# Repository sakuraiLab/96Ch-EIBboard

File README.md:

# 96-channel EIB board
Yuma Osako, Doshisha University (2021)
Tomoya Ohnuki, Kazuki Shiotani, Yuta Tanisumi, Shogo Takamiya

This package is provided free under the terms of the Creative Commons Attribution-NonCommercial-ShareAlike 3.0 IGO License.

This blueprint was generated for the electrophysiological recording of the mice/rats using tetrodes (96ch, 24 tetrodes).

## References
OpenEphys 
An easy-to-assemble, robust, and lightweight drive implant for chronic tetrode recordings in freely moving animals J Voigts, JP Newman, MA Wilson, MT Harnett Journal of Neural Engineering 17 (2), 026044 (https://iopscience.iop.org/article/10.1088/1741-2552/ab77f9/meta)

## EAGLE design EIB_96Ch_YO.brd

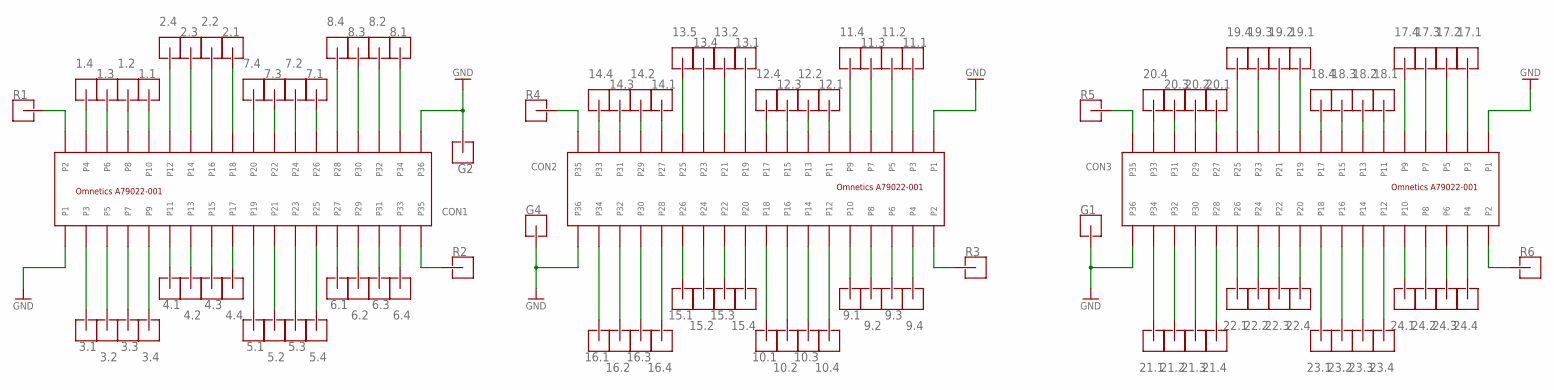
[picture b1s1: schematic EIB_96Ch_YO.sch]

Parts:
1.1, 1.2, 1.3, 1.4, 2.1, 2.2, 2.3, 2.4, 3.1, 3.2, 3.3, 3.4, 4.1, 4.2, 4.3, 4.4, 5.1, 5.2, 5.3, 5.4, 6.1, 6.2, 6.3, 6.4, 7.1, 7.2, 7.3, 7.4, 8.1, 8.2, 8.3, 8.4, 9.1, 9.2, 9.3, 9.4, 10.1, 10.2, 10.3, 10.4, 11.1, 11.2, 11.3, 11.4, 12.1, 12.2, 12.3, 12.4, 13.1, 13.2, 13.4, 13.5, 14.1, 14.2, 14.3, 14.4, 15.1, 15.2, 15.3, 15.4, 16.1, 16.2, 16.3, 16.4, 17.1, 17.2, 17.3, 17.4, 18.1, 18.2, 18.3, 18.4, 19.1, 19.2, 19.3, 19.4, 20.1, 20.2, 20.3, 20.4, 21.1, 21.2, 21.3, 21.4, 22.1, 22.2, 22.3, 22.4, 23.1, 23.2, 23.3, 23.4, 24.1, 24.2, 24.3, 24.4: HOLE_L_G_PIN_V5; LARGE_GOLD_PIN_V5
CON1, CON2, CON3: A79022-001_MALESMD; A79026-001_MALE
G1, G2, G4: HOLE_L_G_PIN_V5; LARGE_GOLD_PIN_V5
R1, R2, R3, R4, R5, R6: HOLE_L_G_PIN_V5; LARGE_GOLD_PIN_V5

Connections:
GND: CON1.P1, CON1.P36, CON2.P1, CON2.P36, CON3.P1, CON3.P36, G1.P$1, G2.P$1, G4.P$1
unnamed: 11.2.P$1, CON2.P5
unnamed: 11.3.P$1, CON2.P7
unnamed: 11.4.P$1, CON2.P9
unnamed: 14.4.P$1, CON2.P33
unnamed: 16.2.P$1, CON2.P32
unnamed: 16.1.P$1, CON2.P34
unnamed: 12.1.P$1, CON2.P11
unnamed: 16.3.P$1, CON2.P30
unnamed: 12.4.P$1, CON2.P17
unnamed: 13.1.P$1, CON2.P19
unnamed: 15.4.P$1, CON2.P20
unnamed: 10.4.P$1, CON2.P12
unnamed: 12.2.P$1, CON2.P13
unnamed: 12.3.P$1, CON2.P15
unnamed: 13.2.P$1, CON2.P21
unnamed: 13.4.P$1, CON2.P23
unnamed: 13.5.P$1, CON2.P25
unnamed: 14.1.P$1, CON2.P27
unnamed: 14.2.P$1, CON2.P29
unnamed: 14.3.P$1, CON2.P31
unnamed: 10.1.P$1, CON2.P18
unnamed: 11.1.P$1, CON2.P3
unnamed: 9.4.P$1, CON2.P4
unnamed: 9.3.P$1, CON2.P6
unnamed: 9.2.P$1, CON2.P8
unnamed: 10.3.P$1, CON2.P14
unnamed: 10.2.P$1, CON2.P16
unnamed: 9.1.P$1, CON2.P10
unnamed: 16.4.P$1, CON2.P28
unnamed: 15.1.P$1, CON2.P26
unnamed: 15.3.P$1, CON2.P22
unnamed: 15.2.P$1, CON2.P24
unnamed: CON1.P2, R1.P$1
unnamed: CON2.P2, R3.P$1
unnamed: CON2.P35, R4.P$1
unnamed: CON1.P35, R2.P$1
unnamed: 3.2.P$1, CON1.P5
unnamed: 3.3.P$1, CON1.P7
unnamed: 3.4.P$1, CON1.P9
unnamed: 4.1.P$1, CON1.P11
unnamed: 4.2.P$1, CON1.P13
unnamed: 4.3.P$1, CON1.P15
unnamed: 5.2.P$1, CON1.P21
unnamed: 5.3.P$1, CON1.P23
unnamed: 5.4.P$1, CON1.P25
unnamed: 7.4.P$1, CON1.P20
unnamed: 7.3.P$1, CON1.P22
unnamed: 7.2.P$1, CON1.P24
unnamed: 4.4.P$1, CON1.P17
unnamed: 5.1.P$1, CON1.P19
unnamed: 7.1.P$1, CON1.P26
unnamed: 2.1.P$1, CON1.P18
unnamed: 3.1.P$1, CON1.P3
unnamed: 1.4.P$1, CON1.P4
unnamed: 1.3.P$1, CON1.P6
unnamed: 1.2.P$1, CON1.P8
unnamed: 2.4.P$1, CON1.P12
unnamed: 2.3.P$1, CON1.P14
unnamed: 2.2.P$1, CON1.P16
unnamed: 1.1.P$1, CON1.P10
unnamed: 6.4.P$1, CON1.P33
unnamed: 6.1.P$1, CON1.P27
unnamed: 6.2.P$1, CON1.P29
unnamed: 6.3.P$1, CON1.P31
unnamed: 8.1.P$1, CON1.P34
unnamed: 8.2.P$1, CON1.P32
unnamed: 8.3.P$1, CON1.P30
unnamed: 8.4.P$1, CON1.P28
unnamed: 20.4.P$1, CON3.P33
unnamed: CON3.P35, R5.P$1
unnamed: 20.3.P$1, CON3.P31
unnamed: 20.2.P$1, CON3.P29
unnamed: 20.1.P$1, CON3.P27
unnamed: 19.4.P$1, CON3.P25
unnamed: 19.3.P$1, CON3.P23
unnamed: 19.2.P$1, CON3.P21
unnamed: 19.1.P$1, CON3.P19
unnamed: 18.4.P$1, CON3.P17
unnamed: 18.3.P$1, CON3.P15
unnamed: 18.2.P$1, CON3.P13
unnamed: 18.1.P$1, CON3.P11
unnamed: 17.4.P$1, CON3.P9
unnamed: 17.3.P$1, CON3.P7
unnamed: 17.2.P$1, CON3.P5
unnamed: 17.1.P$1, CON3.P3
unnamed: CON3.P2, R6.P$1
unnamed: 24.4.P$1, CON3.P4
unnamed: 24.3.P$1, CON3.P6
unnamed: 24.2.P$1, CON3.P8
unnamed: 24.1.P$1, CON3.P10
unnamed: 23.4.P$1, CON3.P12
unnamed: 23.3.P$1, CON3.P14
unnamed: 23.2.P$1, CON3.P16
unnamed: 23.1.P$1, CON3.P18
unnamed: 22.4.P$1, CON3.P20
unnamed: 22.3.P$1, CON3.P22
unnamed: 22.2.P$1, CON3.P24
unnamed: 22.1.P$1, CON3.P26
unnamed: 21.4.P$1, CON3.P28
unnamed: 21.3.P$1, CON3.P30
unnamed: 21.2.P$1, CON3.P32
unnamed: 21.1.P$1, CON3.P34

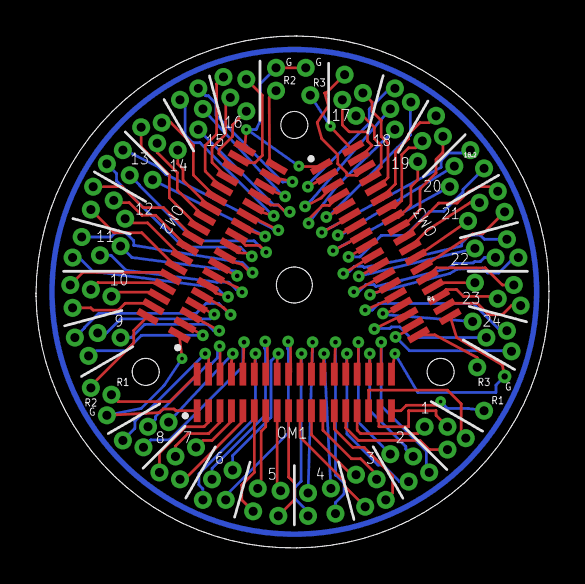
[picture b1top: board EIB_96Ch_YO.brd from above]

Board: 2 copper layers, 28.5 x 28.4 mm, 108 parts (0 on the bottom side), 103 nets.
